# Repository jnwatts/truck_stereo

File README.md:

# truck_stereo
A very simple ESP32+RN52 stereo module for an old truck

I really want to make a much nicer "head unit", but as I can't seem to keep focused on that much larger project I figured I would throw this together with minimal effort for my minimal effort truck.

If you find something here useful, great! Just make sure you attribute me somewhere in your software & source. :-)

Software is licensed under the [MIT license](https://opensource.org/licenses/MIT).
Hardare is licensed under the [Creative Commons Attribution 4.0 International license (CC-BY-4.0)](https://creativecommons.org/licenses/by/4.0/)

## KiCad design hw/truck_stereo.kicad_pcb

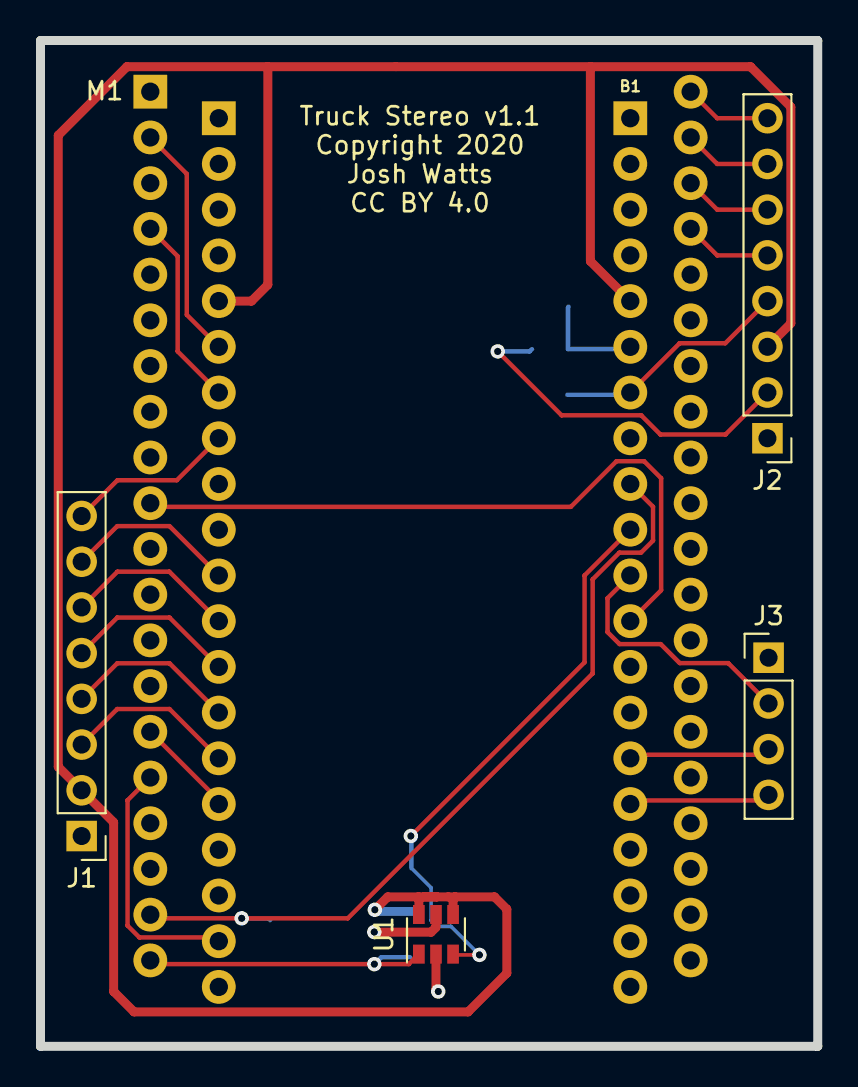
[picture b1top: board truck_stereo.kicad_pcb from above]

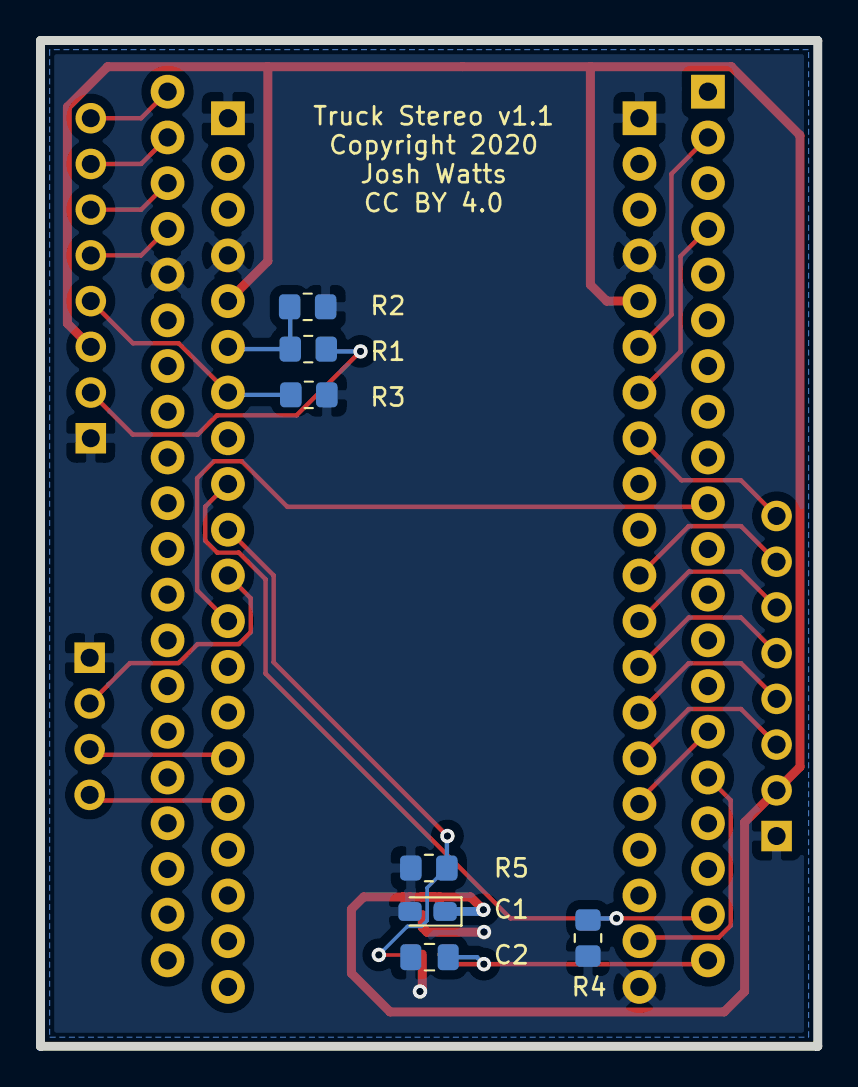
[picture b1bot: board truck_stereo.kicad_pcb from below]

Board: 2 copper layers, 43.2 x 55.9 mm, 13 parts (7 on the bottom side), 26 nets.

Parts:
B1: ESP32_THING_W_ANT_KEEPOUT; ESP32_THING_NO_ANT
C1: 1uF; CP_EIA-2012-15_AVX-P_Pad1.30x1.05mm_HandSolder
C2: 0.1uF; C_0805_2012Metric_Pad1.18x1.45mm_HandSolder
J1, J2: Conn_01x08_Male; PinHeader_1x08_P2.54mm_Vertical
J3: Conn_01x04_Male; PinHeader_1x04_P2.54mm_Vertical
M1: BLUETOOTH-RN-52; sparkfun-rn-52
R1: 1k; R_0805_2012Metric_Pad1.20x1.40mm_HandSolder
R2, R3, R4, R5: 100k; R_0805_2012Metric_Pad1.20x1.40mm_HandSolder
U1: TPS22929D; SOT-23-6

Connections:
+3V3: B1.5, B1.36, C1.1, J1.2, J2.3, U1.4, U1.6
/DISP_CS: B1.29, J1.6
/DISP_DC: B1.33, J1.8
/DISP_MISO: B1.26, J1.3
/DISP_MOSI: B1.27, J1.4
/DISP_RST: B1.30, J1.7
/DISP_SCLK: B1.28, J1.5
/ESP32_PWREN: J2.2, R1.1
/ESP32_RST: B1.6, R1.2, R2.1
/ESP32_RX: B1.25, M1.15
/ESP32_TX: B1.22, M1.16
/REMOTE_EN: B1.7, J2.4, R3.1
/RN52_FRST: B1.34, M1.4
/RN52_INT: B1.35, M1.2
/RN52_PWREN: B1.9, M1.19, R4.1
/RN52_VDD: C2.1, M1.20, U1.1
/RN52_VDD_SW: B1.10, R5.1, U1.3
/ROT_A: B1.16, J3.4
/ROT_B: B1.15, J3.3
/ROT_SW: B1.11, J3.2
/SPKR_L+: J2.8, M1.40
/SPKR_L-: J2.6, M1.38
/SPKR_R+: J2.7, M1.39
/SPKR_R-: J2.5, M1.37
/~RN52_CMD: B1.12, M1.10
GND: B1.1, B1.4, B1.21, B1.37, B1.40, C1.2, C2.2, J1.1, J2.1, J3.1, M1.36, R2.2, R3.2, R4.2, R5.2, U1.2, U1.5

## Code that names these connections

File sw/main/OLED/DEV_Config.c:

#include <driver/spi_common.h>
#include <driver/spi_master.h>
#include <freertos/task.h>
#include <stdio.h>
#include <stdlib.h>
#include <string.h>

#include "DEV_Config.h"

//OLED GPIO
static const gpio_num_t DISP_MOSI = GPIO_NUM_23;
static const gpio_num_t DISP_SCLK = GPIO_NUM_18;
static const gpio_num_t DISP_DC = GPIO_NUM_4; // HACK: Relocated from 2 due to USB programming interference
static const gpio_num_t DISP_RST = GPIO_NUM_15;
static const gpio_num_t DISP_CS = GPIO_NUM_5;
static const spi_host_device_t DISP_SPI_BUS = SPI3_HOST;

static const spi_bus_config_t bus_config = {
    .miso_io_num = -1,
    .mosi_io_num = DISP_MOSI,
    .sclk_io_num = DISP_SCLK,
    .quadwp_io_num = -1,
    .quadhd_io_num = -1,
    .max_transfer_sz = 128*128/2, // Worst case, entire buffer ram
};

static const spi_device_interface_config_t dev_config = {
    .mode = 0,
    .clock_speed_hz = SPI_MASTER_FREQ_20M,
    .spics_io_num = DISP_CS,
    .queue_size=16,
};

static spi_device_handle_t spi_handle;

void OLED_Sys_Init(void)
{
    // init gpio
    ESP_ERROR_CHECK(gpio_reset_pin(DISP_DC));
    ESP_ERROR_CHECK(gpio_reset_pin(DISP_RST));

    ESP_ERROR_CHECK(gpio_pullup_dis(DISP_DC));
    ESP_ERROR_CHECK(gpio_pullup_dis(DISP_RST));

    ESP_ERROR_CHECK(gpio_set_level(DISP_DC, 0));
    ESP_ERROR_CHECK(gpio_set_level(DISP_RST, 0));

    ESP_ERROR_CHECK(gpio_set_direction(DISP_DC, GPIO_MODE_OUTPUT));
    ESP_ERROR_CHECK(gpio_set_direction(DISP_RST, GPIO_MODE_OUTPUT));

    // init spi module
    ESP_ERROR_CHECK(spi_bus_initialize(DISP_SPI_BUS, &bus_config, DISP_SPI_BUS));
    ESP_ERROR_CHECK(spi_bus_add_device(DISP_SPI_BUS, &dev_config, &spi_handle));
}

static void OLED_Write_Byte(uint8_t value, uint8_t Cmd)
{
    spi_transaction_t desc = {
        .flags = SPI_TRANS_USE_TXDATA,
        .tx_data = { value },
        .length = 8,
    };
    gpio_set_level(DISP_DC, Cmd);
    spi_device_transmit(spi_handle, &desc);
}

static void OLED_Write_Block(uint8_t *data, uint16_t len, uint8_t Cmd)
{
    spi_transaction_t desc = {
        .flags = 0,
        .tx_buffer = data,
        .length = len * 8,
    };
    gpio_set_level(DISP_DC, Cmd);
    spi_device_transmit(spi_handle, &desc);
}

void OLED_Reset(void)
{
    gpio_set_level(DISP_RST, 1);
    OLED_Delay_ms(100);
    gpio_set_level(DISP_RST, 0);
    OLED_Delay_ms(100);
    gpio_set_level(DISP_RST, 1);
    OLED_Delay_ms(100);
}

void OLED_WriteReg(uint8_t reg)
{
    OLED_Write_Byte(reg, OLED_CMD);
}

void OLED_WriteRegBlock(uint8_t *data, uint16_t len)
{
    OLED_Write_Block(data, len, OLED_CMD);
}

void OLED_WriteData(uint8_t data)
{
    OLED_Write_Byte(data, OLED_RAM);
}

void OLED_WriteDataBlock(uint8_t *data, uint16_t len)
{
    OLED_Write_Block(data, len, OLED_RAM);
}

void OLED_Delay_ms(uint32_t ms)
{
    vTaskDelay(ms / portTICK_PERIOD_MS);
}

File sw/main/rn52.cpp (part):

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
static const gpio_num_t rn52_tx_pin = GPIO_NUM_21;
static const gpio_num_t rn52_rx_pin = GPIO_NUM_22;
static const gpio_num_t rn52_vdd_sw_pin = GPIO_NUM_27;
static const gpio_num_t rn52_cmdn_pin = GPIO_NUM_25;
static const gpio_num_t rn52_pwren_pin = GPIO_NUM_14;
static const gpio_num_t rn52_frst_pin = GPIO_NUM_17;
static const gpio_num_t rn52_int_pin = GPIO_NUM_16;

static const int rn52_uart_num = UART_NUM_2;
static const int rn52_uart_buff_size = 512;
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
void RN52::initGpio(void)
{
    ESP_ERROR_CHECK(gpio_reset_pin(rn52_vdd_sw_pin));
    ESP_ERROR_CHECK(gpio_reset_pin(rn52_cmdn_pin));
    ESP_ERROR_CHECK(gpio_reset_pin(rn52_pwren_pin));
    ESP_ERROR_CHECK(gpio_reset_pin(rn52_frst_pin));
    ESP_ERROR_CHECK(gpio_reset_pin(rn52_int_pin));

    ESP_ERROR_CHECK(gpio_pullup_dis(rn52_vdd_sw_pin));
    ESP_ERROR_CHECK(gpio_pullup_dis(rn52_cmdn_pin));
    ESP_ERROR_CHECK(gpio_pullup_dis(rn52_pwren_pin));
    ESP_ERROR_CHECK(gpio_pullup_dis(rn52_frst_pin));
    ESP_ERROR_CHECK(gpio_pullup_dis(rn52_int_pin));

    ESP_ERROR_CHECK(gpio_set_level(rn52_vdd_sw_pin, 0));
    ESP_ERROR_CHECK(gpio_set_level(rn52_cmdn_pin, 0)); // Default to command mode!
    ESP_ERROR_CHECK(gpio_set_level(rn52_pwren_pin, 0));
    ESP_ERROR_CHECK(gpio_set_level(rn52_frst_pin, 0));

    ESP_ERROR_CHECK(gpio_set_direction(rn52_vdd_sw_pin, GPIO_MODE_OUTPUT));
    ESP_ERROR_CHECK(gpio_set_direction(rn52_cmdn_pin, GPIO_MODE_OUTPUT));
    ESP_ERROR_CHECK(gpio_set_direction(rn52_pwren_pin, GPIO_MODE_OUTPUT));
    ESP_ERROR_CHECK(gpio_set_direction(rn52_frst_pin, GPIO_MODE_OUTPUT));
    ESP_ERROR_CHECK(gpio_set_direction(rn52_int_pin, GPIO_MODE_INPUT));

    ESP_ERROR_CHECK(gpio_set_intr_type(rn52_int_pin, GPIO_INTR_NEGEDGE));
    ESP_ERROR_CHECK(gpio_isr_handler_add(rn52_int_pin, RN52::intr, this));
}

void RN52::setPower(bool enabled)
{
    gpio_set_level(rn52_vdd_sw_pin, (enabled ? 1 : 0));
}

void RN52::setEnabled(bool enabled)
{
    gpio_set_level(rn52_pwren_pin, (enabled ? 1 : 0));
}

bool RN52::setCommand(bool enabled)
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
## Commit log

2020-11-23 Version 1.0
2020-11-24 SW: Version 1.0.0
2020-11-27 Move rotary-encoder to components
2020-11-27 OLED: Import from Waveshare's sd1327 examples
    https://www.waveshare.com/wiki/1.5inch_OLED_Module
2020-11-27 OLED: Whitespace cleanup
2020-11-30 OLED: Rewrite DEV_Config for my application
2020-11-30 ugui: Add PutText() and WindowGetActive() public APIs
2020-11-30 OLED: Fix buggy column logic & make use of faster block writes
    SSD1327 works in 4-bit pixels packed in 8-bit columns: All functions expect arguments to be in *columns*.
2020-11-30 WIP: ugui: Improve bitmap support
    Not yet tested!
2020-11-30 OLED: Remove unused and broken set-cursor
    SSD1327 does not have a set-cursor function, and the functions used here set the render window to a 1x1 pixel!!
2020-11-30 hw: Rename schematic to include version
2020-11-30 OLED: Replace byte-by-byte with block write
2020-11-30 Makefile: Break out build from idf.py
2020-11-30 docs: Add DS for SSD1327
2020-11-30 ugui: HACK: Fix non-printable issues
    My editor keeps truncating the new-line following these non-printables leading to unintended edits... so just remove them.
2020-11-30 ugui: Implement post/pre render event for windows
    This allows custom window implementations built on top of the existing UG_WINDOW logic
2020-11-30 OLED: Implement block-write for registers
2020-11-30 Import gh:achimdoebler/UGUI
    From ce0bccb5b7d4877c42081419fccadf7aa5727303
2020-11-30 OLED: All I/O logic moved to DEV_Config
2020-11-30 OLED: Be more defensive about valid color values
2020-11-30 WIP: UGUICPP: Implement C++ API around UGUI
    The goal is to wrap 100% of the existing API while adding no more than is aboslutely necessary. Any additional functionality desired should be done by sub-classing from existing classes.
    TODO:
    - button
    - image
    - checkbox
2020-11-30 ugui: Add const to string functions
2020-11-30 OLED: Avoid wasting memory, only u8 is needed
2020-11-30 ugui: Allow objects to be full width & height
    The code currently allows a_rel.xs to be 0, so why limit xe to wnd->xe - 1?
2020-11-30 WIP: hw: fixups
2020-11-30 ugui: Fix compiler warnings
2020-11-30 ugui: Reduce #ifdef's for post/pre render events
2020-11-30 Ignore old sdkconfig
2020-11-30 loop: Invoke 0 or more callbacks once per call to Loop::loop()
    Implements an observer pattern for the "loop" event. Callbacks that return false are removed from the list.
2020-11-30 WIP: rn52: Use new loop() style
2020-11-30 WIP: system: Enable FONT_4X6 for Menu window
2020-11-30 WIP: system.h
2020-11-30 WIP: display: Tone things down a bit
2020-11-30 WIP: main: Integrate input
2020-11-30 WIP: display
2020-11-30 UI: Rotating textbox
    Allows display of strings wider than visible area
2020-11-30 WIP: main
2020-11-30 WIP: UI: Main
2020-11-30 WIP: Input
2020-11-30 WIP: UI: Menu window
    TODO:
    - Input handling for SELECT & LONG_SELECT
    - Perhaps store callback or pointer for "previous menu" or "null" to return to main?
    - Move Input::msg_t to other global scope... maybe?
2020-11-30 WIP: input: Rewrite
    - Implement LONG_SELECT
    - Improve debounce
    - Use new loop() style
2020-11-30 WIP: CMake
2020-11-30 WIP: UI: Window
    Provides additional logic not provided by UGUI API
2020-11-30 Docs: Brainstorming for UI interactions
2020-11-30 WIP: input: Replace callback with std::functional

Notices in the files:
sw/main/rn52.cpp:
Copyright (c) 2020 Josh Watts
hw/truck_stereo.kicad_pcb:
Copyright 2020
CC BY 4.0
